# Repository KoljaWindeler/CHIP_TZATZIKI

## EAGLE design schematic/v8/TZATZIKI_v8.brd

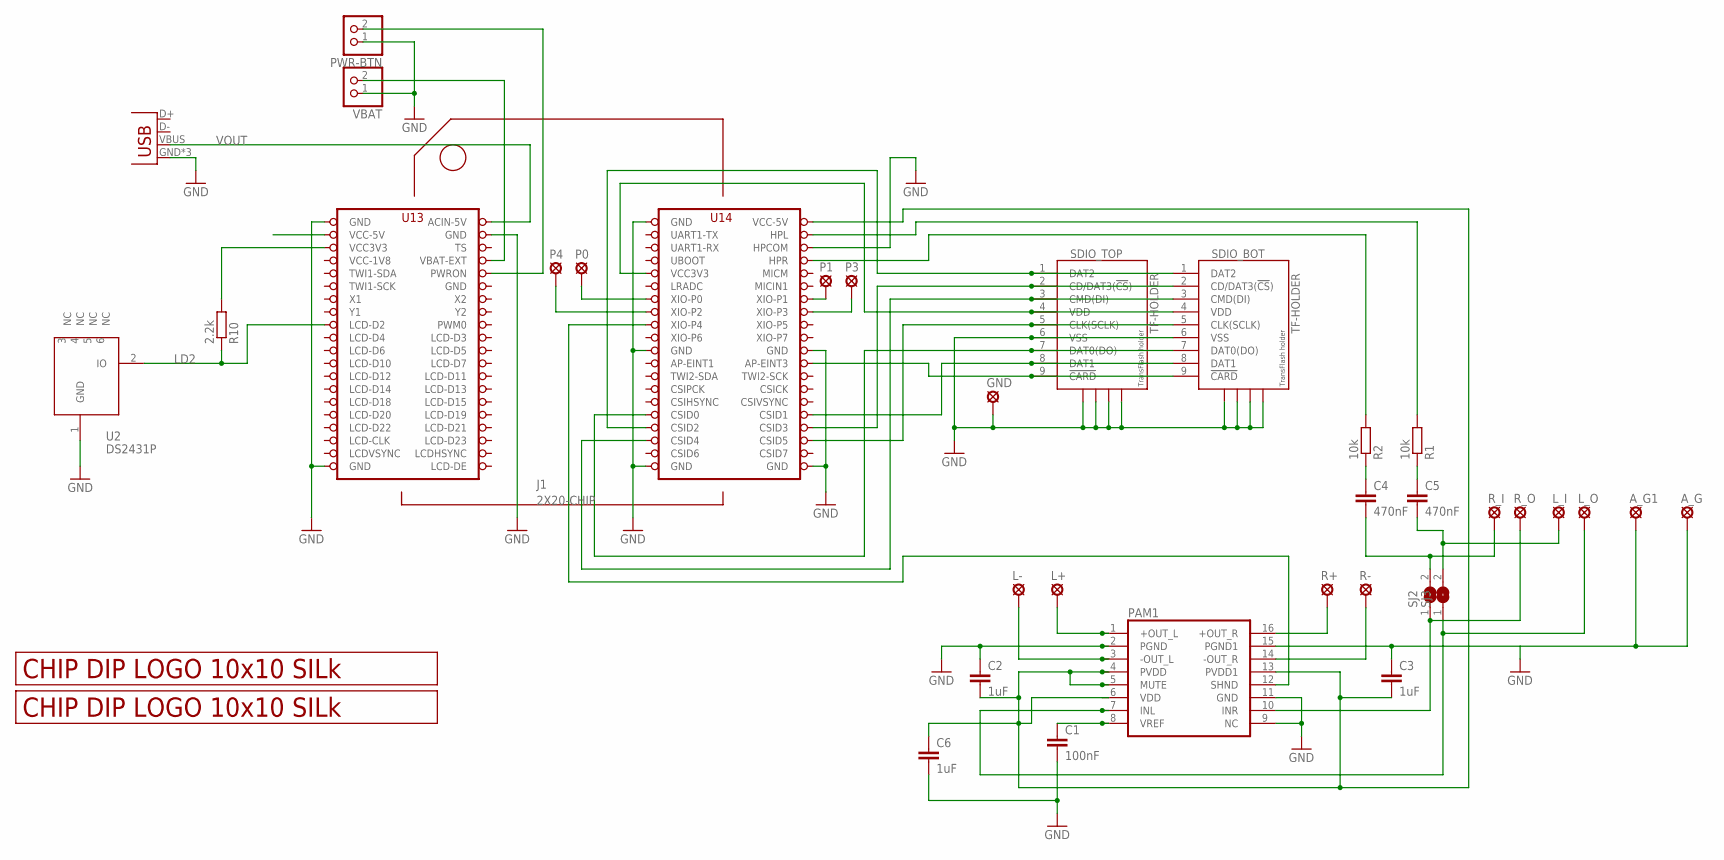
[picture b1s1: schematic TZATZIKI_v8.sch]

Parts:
A_G, A_G1: SE11
C1: 100nF; C0805
C2, C3, C6: 1uF; C0805
C4, C5: 470nF; C0805
GND: SE11
J1: 2X20-CHIP; 2X20CHIP_OFFSET-TH
L+: SE11
L-: SE11
L_I: SE11
L_O: SE11
P0, P1, P3, P4: SE11
PAM1: PAM8403; SOP-16
POWER_USB: USBUSB-MICROB-SMT-DIP; USB-MICROB-SMT-DIP
PWR-BTN: PINHD-1X2; 1X02
R1, R2: 10k; R0805
R10: 2.2k; R0805
R+: SE11
R-: SE11
R_I: SE11
R_O: SE11
SDIO_BOT: TF-HOLDER; TF-PULL
SDIO_TOP: TF-HOLDER; TF-PULL
SJ2, SJ3: SJ
U2: DS2431P; TSOC6
U$1, U$2: LOGO_10X10_SILK; LOGO2_10X10_SILK
VBAT: PINHD-1X2; 1X02

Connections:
GND: A_G.MP, A_G1.MP, C1.2, C2.1, C3.1, C6.2, GND.MP, J1.GND@1 (GND), J1.GND@2 (GND), J1.GND@3 (GND), J1.GND@4 (GND), J1.GND@5 (GND), J1.GND@6 (GND), J1.GND@7 (GND), J1.GND@8 (GND), J1.GND@10 (GND), J1.HPCOM, PAM1.2 (PGND), PAM1.9 (NC), PAM1.11 (GND), PAM1.15 (PGND1), POWER_USB.GND, POWER_USB.MT1 (GND), POWER_USB.MT2 (GND), PWR-BTN.1, SDIO_BOT.6 (VSS), SDIO_BOT.S1, SDIO_BOT.S2, SDIO_BOT.S3, SDIO_BOT.S4, SDIO_TOP.6 (VSS), SDIO_TOP.S1, SDIO_TOP.S2, SDIO_TOP.S3, SDIO_TOP.S4, U2.1 (GND), VBAT.1
LD2: J1.LCD-D2, R10.1, U2.2 (IO)
unnamed: J1.VCC3V3, R10.2
unnamed: J1.CSID3, SDIO_BOT.2 (CD/DAT3(!CS!)), SDIO_TOP.2 (CD/DAT3(!CS!))
unnamed: J1.CSID0, SDIO_BOT.7 (DAT0(DO)), SDIO_TOP.7 (DAT0(DO))
unnamed: J1.CSID4, SDIO_BOT.3 (CMD(DI)), SDIO_TOP.3 (CMD(DI))
unnamed: J1.CSID5, SDIO_BOT.5 (CLK(SCLK)), SDIO_TOP.5 (CLK(SCLK))
unnamed: J1.CSID1, SDIO_BOT.8 (DAT1), SDIO_TOP.8 (DAT1)
unnamed: C2.2, C3.2, C6.1, J1.VCC5V@1 (VCC-5V), PAM1.4 (PVDD), PAM1.5 (MUTE), PAM1.6 (VDD), PAM1.13 (PVDD1)
unnamed: J1.CSID2, SDIO_BOT.1 (DAT2), SDIO_TOP.1 (DAT2)
unnamed: J1.VCC3V3@1 (VCC3V3), SDIO_BOT.4 (VDD), SDIO_TOP.4 (VDD)
unnamed: L+.MP, PAM1.1 (+OUT_L)
unnamed: L-.MP, PAM1.3 (-OUT_L)
unnamed: PAM1.16 (+OUT_R), R+.MP
unnamed: PAM1.14 (-OUT_R), R-.MP
unnamed: L_O.MP, PAM1.7 (INL), SJ3.1
unnamed: J1.AP-EINT3, SDIO_BOT.9 (!CARD), SDIO_TOP.9 (!CARD)
unnamed: PAM1.10 (INR), R_O.MP, SJ2.1
unnamed: J1.HPL, R1.2
unnamed: C1.1, PAM1.8 (VREF)
unnamed: C4.1, R2.1
unnamed: C5.1, R1.1
unnamed: J1.XIO-P1, P1.MP
unnamed: J1.XIO-P3, P3.MP
unnamed: J1.XIO-P0, P0.MP
unnamed: J1.XIO-P2, P4.MP
unnamed: J1.XIO-P4, PAM1.12 (SHND)
unnamed: J1.BAT (VBAT-EXT), VBAT.2
unnamed: J1.PWRON, PWR-BTN.2
unnamed: J1.HPR, R2.2
unnamed: C4.2, R_I.MP, SJ2.2
unnamed: C5.2, L_I.MP, SJ3.2
VCC-1V8: J1.VCC1V8 (VCC-1V8)
VOUT: J1.CHG-IN (ACIN-5V), POWER_USB.VBUS

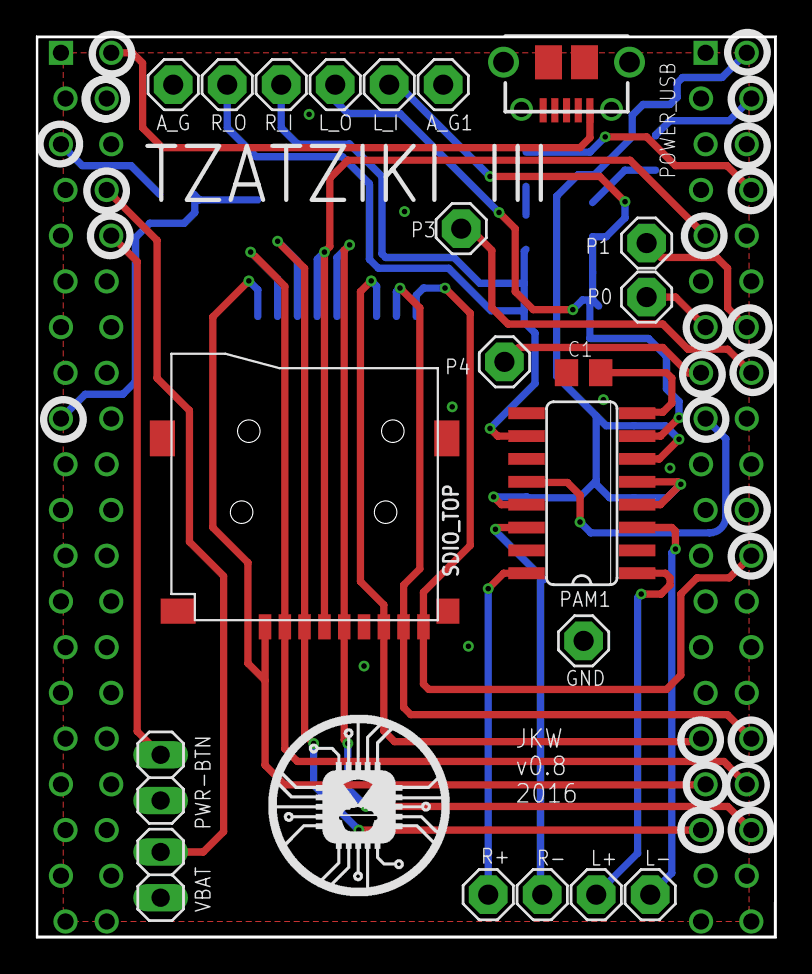
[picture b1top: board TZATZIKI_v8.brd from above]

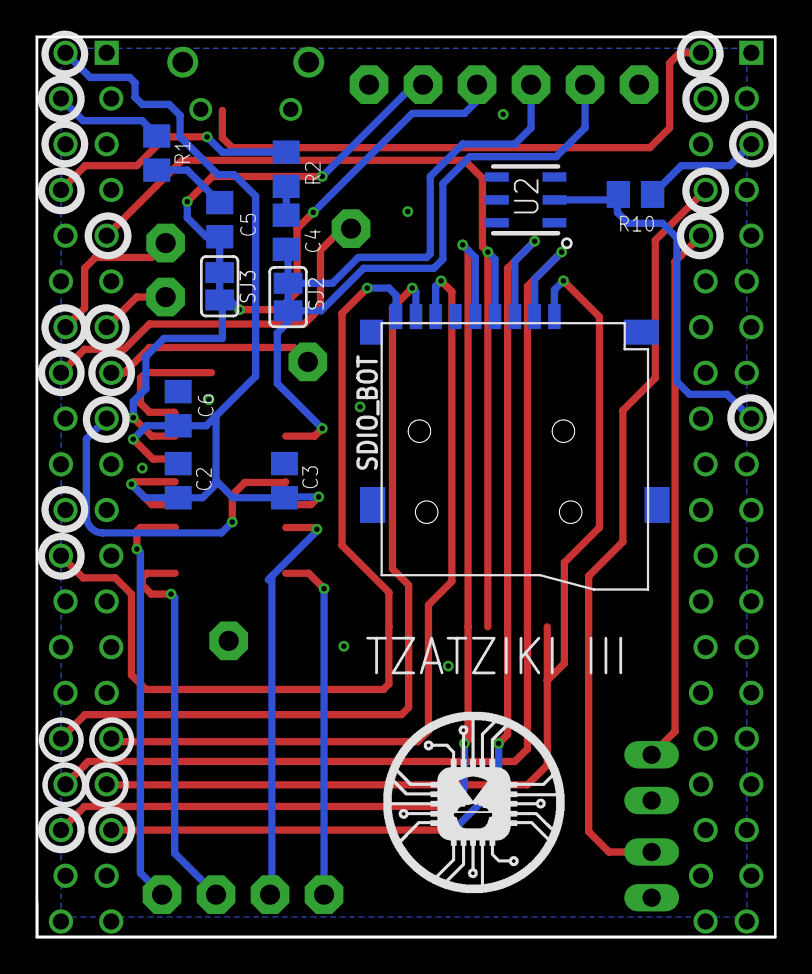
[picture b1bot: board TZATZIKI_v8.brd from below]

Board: 2 copper layers, 41.0 x 50.0 mm, 36 parts (13 on the bottom side), 33 nets.

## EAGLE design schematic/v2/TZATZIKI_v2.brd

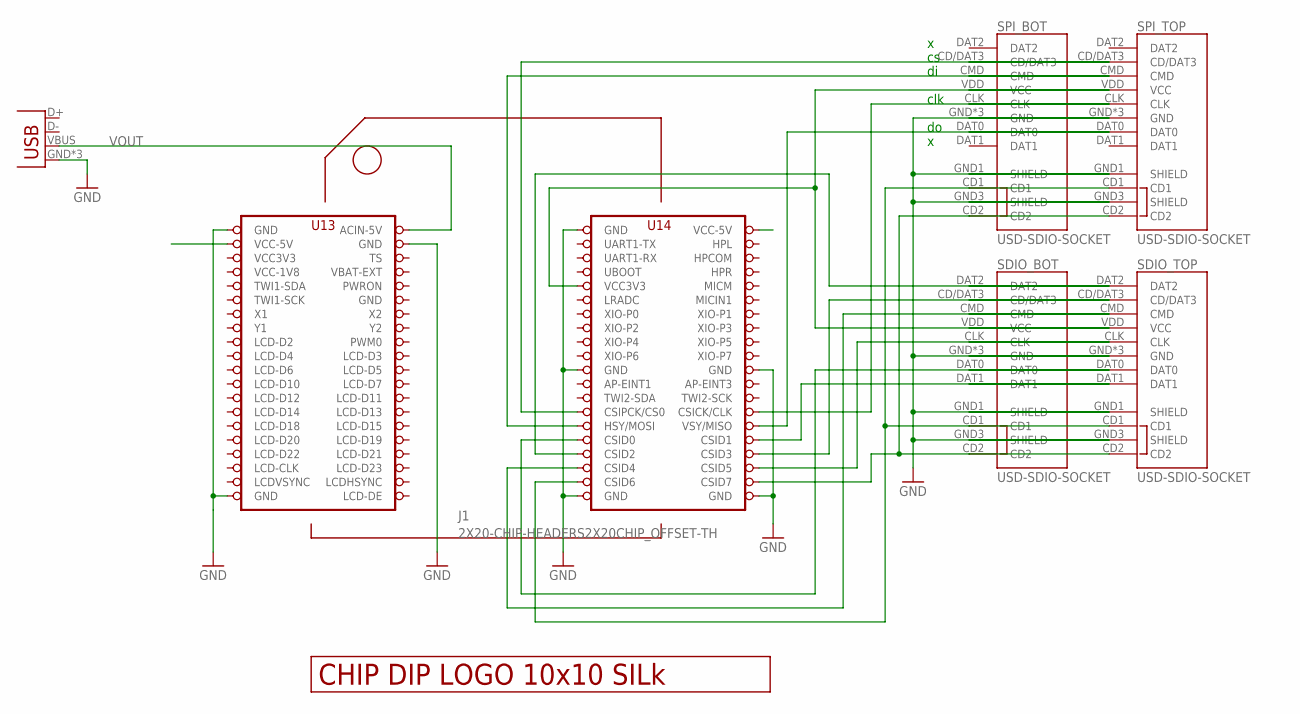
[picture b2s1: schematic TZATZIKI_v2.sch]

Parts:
J1: 2X20-CHIP-HEADERS2X20CHIP_OFFSET-TH; 2X20CHIP_OFFSET-TH
POWER_USB: USBUSB-MICROB-SMT-DIP; USB-MICROB-SMT-DIP
SDIO_BOT: USD-SDIO-SOCKET; MICRO-SD-SOCKET-SDIO
SDIO_TOP: USD-SDIO-SOCKET; MICRO-SD-SOCKET-SDIO
SPI_BOT: USD-SDIO-SOCKET; MICRO-SD-SOCKET-SDIO
SPI_TOP: USD-SDIO-SOCKET; MICRO-SD-SOCKET-SDIO
U$1: LOGO_10X10_SILK

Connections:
GND: J1.GND@1 (GND), J1.GND@2 (GND), J1.GND@3 (GND), J1.GND@4 (GND), J1.GND@5 (GND), J1.GND@6 (GND), J1.GND@7 (GND), J1.GND@8 (GND), J1.GND@10 (GND), POWER_USB.GND, POWER_USB.MT1 (GND), POWER_USB.MT2 (GND), SDIO_BOT.GND, SDIO_BOT.GND1 (SHIELD), SDIO_BOT.GND3 (SHIELD), SDIO_BOT.GND@1 (GND), SDIO_BOT.GND@2 (GND), SDIO_TOP.GND, SDIO_TOP.GND1 (SHIELD), SDIO_TOP.GND3 (SHIELD), SDIO_TOP.GND@1 (GND), SDIO_TOP.GND@2 (GND), SPI_BOT.GND, SPI_BOT.GND1 (SHIELD), SPI_BOT.GND3 (SHIELD), SPI_BOT.GND@1 (GND), SPI_BOT.GND@2 (GND), SPI_TOP.GND, SPI_TOP.GND1 (SHIELD), SPI_TOP.GND3 (SHIELD), SPI_TOP.GND@1 (GND), SPI_TOP.GND@2 (GND)
unnamed: J1.CSID7, SDIO_BOT.CD2, SDIO_TOP.CD2, SPI_BOT.CD2, SPI_TOP.CD2
unnamed: J1.CSID3, SDIO_BOT.CD/DAT3, SDIO_TOP.CD/DAT3
unnamed: J1.CSID0, SDIO_BOT.DAT0, SDIO_TOP.DAT0
unnamed: J1.CSID4, SDIO_BOT.CMD, SDIO_TOP.CMD
unnamed: J1.CSID5, SDIO_BOT.CLK, SDIO_TOP.CLK
unnamed: J1.CSID1, SDIO_BOT.DAT1, SDIO_TOP.DAT1
unnamed: J1.CSID2, SDIO_BOT.DAT2, SDIO_TOP.DAT2
unnamed: J1.VCC3V3@1 (VCC3V3), SDIO_BOT.VDD (VCC), SDIO_TOP.VDD (VCC), SPI_BOT.VDD (VCC), SPI_TOP.VDD (VCC)
unnamed: J1.CSIPCK (CSIPCK/CS0), SPI_BOT.CD/DAT3, SPI_TOP.CD/DAT3
unnamed: J1.CSIHSYNC (HSY/MOSI), SPI_BOT.CMD, SPI_TOP.CMD
unnamed: J1.CSIVSYNC (VSY/MISO), SPI_BOT.DAT0, SPI_TOP.DAT0
unnamed: J1.CSICK (CSICK/CLK), SPI_BOT.CLK, SPI_TOP.CLK
unnamed: J1.CSID6, SDIO_BOT.CD1, SDIO_TOP.CD1, SPI_BOT.CD1, SPI_TOP.CD1
VCC3V3: J1.VCC3V3
VCC-1V8: J1.VCC1V8 (VCC-1V8)
VOUT: J1.CHG-IN (ACIN-5V), POWER_USB.VBUS

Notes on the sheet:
clk

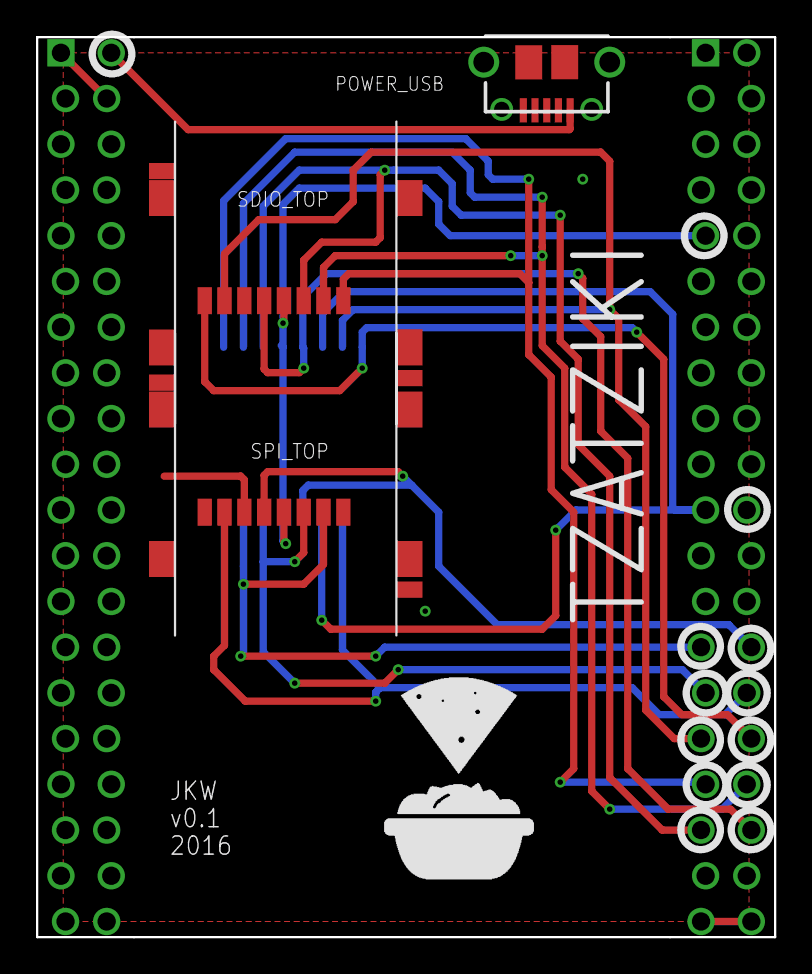
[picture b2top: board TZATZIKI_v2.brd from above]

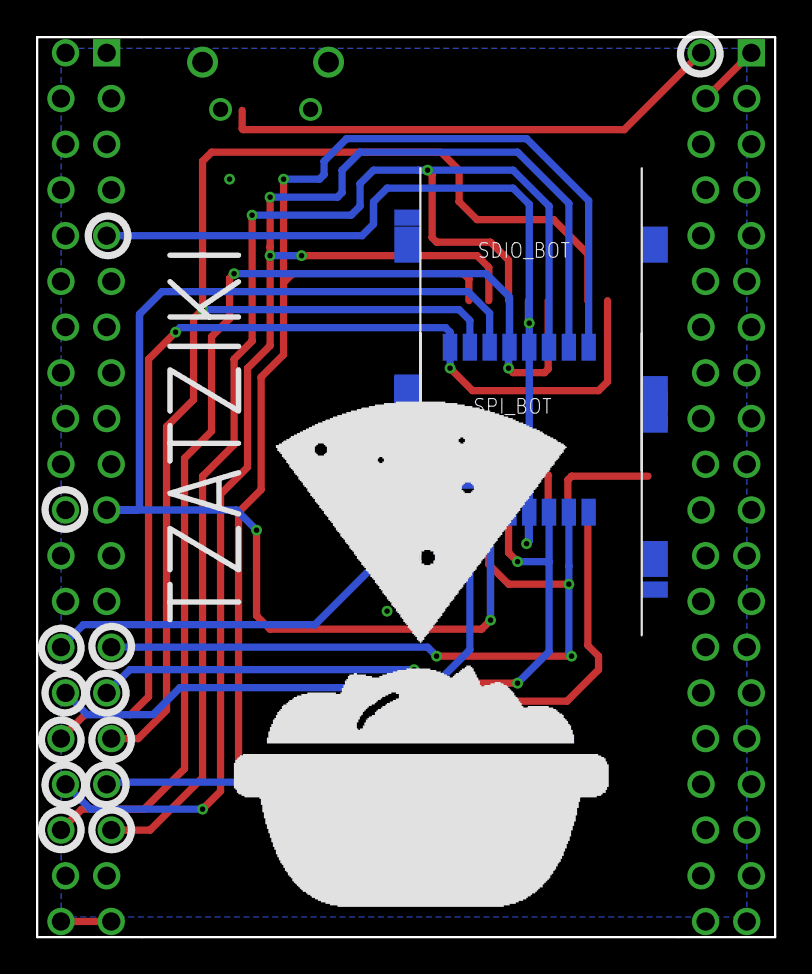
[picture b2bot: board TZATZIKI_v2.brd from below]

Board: 2 copper layers, 41.0 x 50.0 mm, 8 parts (3 on the bottom side), 15 nets.

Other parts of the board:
U$2: LOGO_25X25_SILK

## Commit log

2016-08-04 :space_invader: Added .gitattributes & .gitignore files
2016-08-04 init
2016-08-04 add sdio version
2016-08-05 added fourway version
2016-08-05 added ignore files
2016-08-10 added v4 with card detect pin
2016-08-10 moved to eint3 for Card detection
2016-08-10 added ignore
2016-08-10 compiles
2016-08-10 added working overlay
2016-08-10 stripped down
2016-08-10 added overlay load script
2016-08-10 added gerber
2016-08-10 remove todo
2016-08-11 added test highspeed version
2016-08-13 v5 with bottom further down
2016-08-14 added version 5 with stereo amp
2016-08-14 connected audio gnd
2016-08-15 added shutdown pin control
2016-08-15 datasheet added
2016-08-20 added bat con and pwrbutton
2016-08-20 rotated connector for free passage of the SD card
2016-08-22 removed v2, added 4.3 dtb/dts
2016-08-24 added v6 with smaller holes, ordered!
2016-08-24 removed card detect pin for pchip
2016-08-25 removed gpio from overlay
2016-08-25 card detect invers works
2016-08-28 added v7, 0.9mm drills, ordered as 1.0 thick bord
2016-08-29 added gerber drill file
2016-08-29 moved to correct subfolder
2016-08-29 moved drill to right subfolder
2016-08-31 Added Descriptions
2016-09-08 added simple script with offset 408
2016-09-08 added preliminary v8 version with volume controll and corected Mute, based on 0.8mm holes
2016-09-09 added stereo poti pads
2016-09-09 added stereo pot, holes 0.9 todo
